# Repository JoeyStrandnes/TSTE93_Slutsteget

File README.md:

# TSTE93_Slutsteget
Projekt för kursen TSTE93

### Electronics

### Case

### Functional diagram

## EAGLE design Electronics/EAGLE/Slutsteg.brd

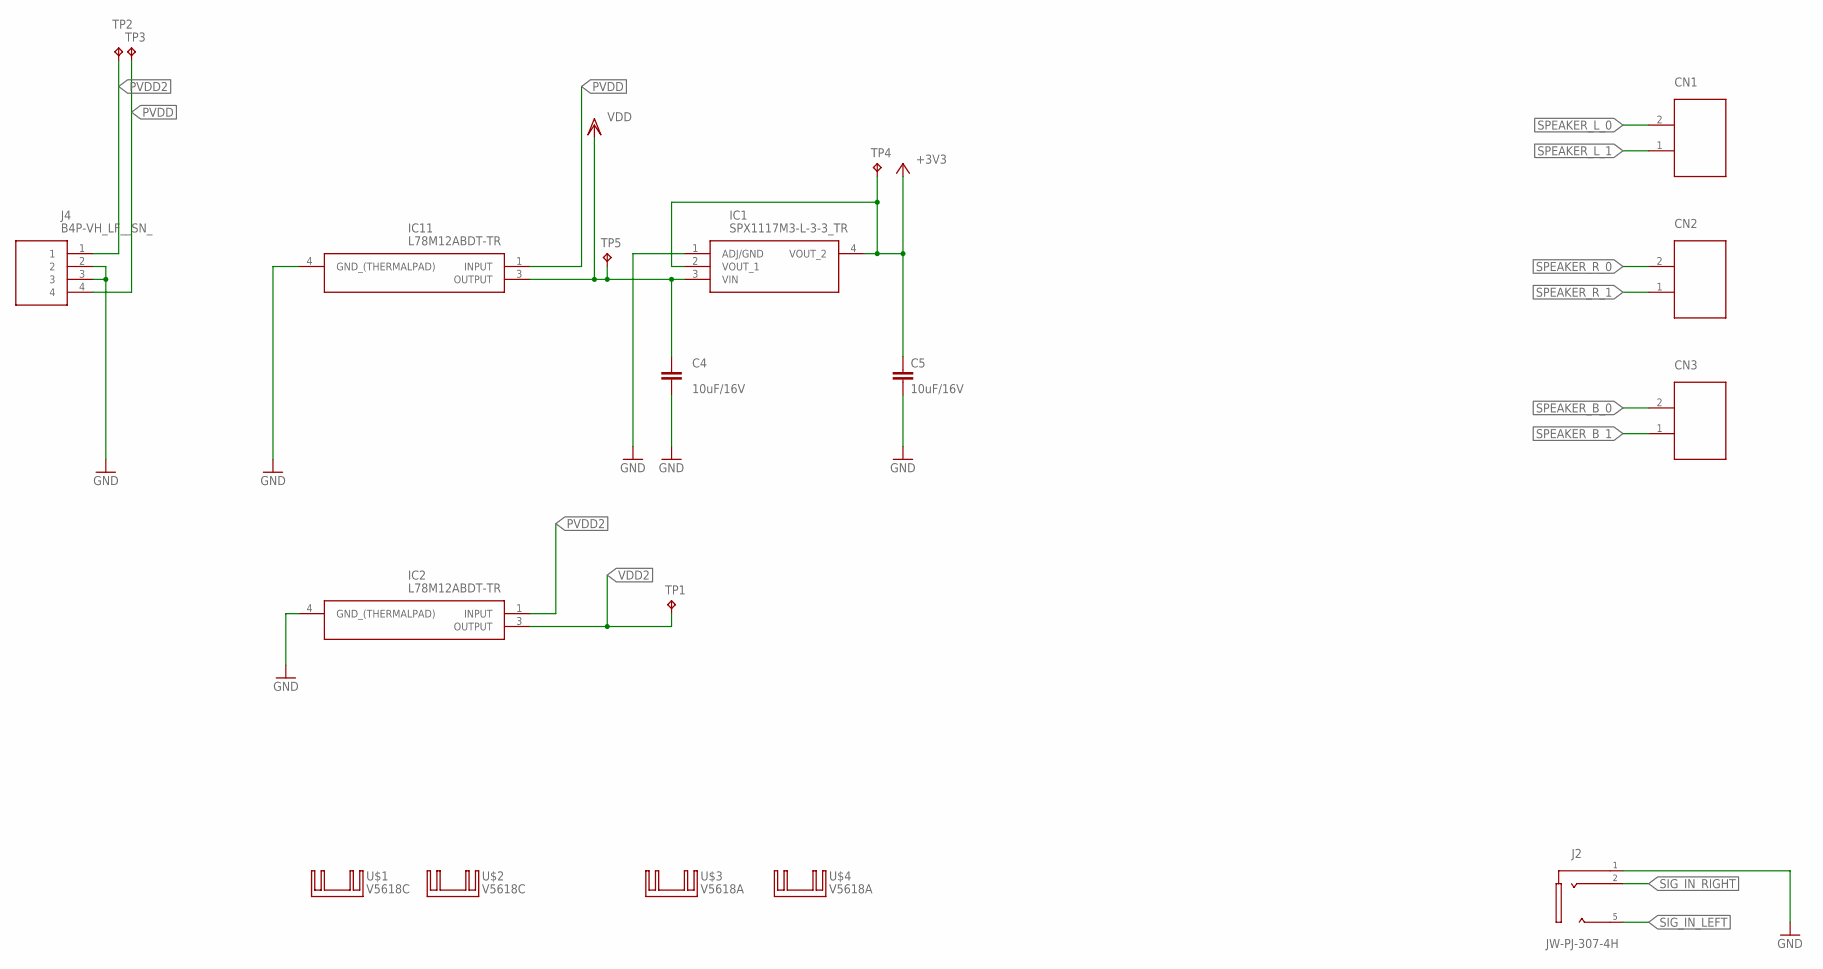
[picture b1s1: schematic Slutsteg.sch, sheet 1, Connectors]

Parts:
C4, C5: 10uF/16V; C0805
CN1, CN2, CN3: OSTYK33102030-2; OSTYK33108030-2
IC1: SPX1117M3-L-3-3_TR; SOT230P700X180-4N
IC2, IC11: L78M12ABDT-TR; TO228P972X240-3N
J2: JW-PJ-307-4H
J4: B4P-VH_LF__SN_; SHDR4W114P0X396_1X4_1578X850X9
TP1: TPB2,54; B2,54
TP2, TP3, TP4, TP5: TPB1,27; B1,27
U$1, U$2: V5618C
U$3, U$4: V5618A

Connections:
+3V3: C5.1, IC1.2 (VOUT_1), IC1.4 (VOUT_2), TP4.TP; also elsewhere on the board
GND: C4.2, C5.2, IC1.1 (ADJ/GND), IC2.4 (GND_(THERMALPAD)), IC11.4 (GND_(THERMALPAD)), J2.1, J4.2, J4.3; also elsewhere on the board
PVDD: IC11.1 (INPUT), J4.4, TP3.TP; also elsewhere on the board
PVDD2: IC2.1 (INPUT), J4.1, TP2.TP; also elsewhere on the board
SIG_IN_LEFT: J2.5; also elsewhere on the board
SIG_IN_RIGHT: J2.2; also elsewhere on the board
SPEAKER_B_0: CN3.2; also elsewhere on the board
SPEAKER_B_1: CN3.1; also elsewhere on the board
SPEAKER_L_0: CN1.2; also elsewhere on the board
SPEAKER_L_1: CN1.1; also elsewhere on the board
SPEAKER_R_0: CN2.2; also elsewhere on the board
SPEAKER_R_1: CN2.1; also elsewhere on the board
VDD: C4.1, IC1.3 (VIN), IC11.3 (OUTPUT), TP5.TP; also elsewhere on the board
VDD2: IC2.3 (OUTPUT), TP1.TP; also elsewhere on the board

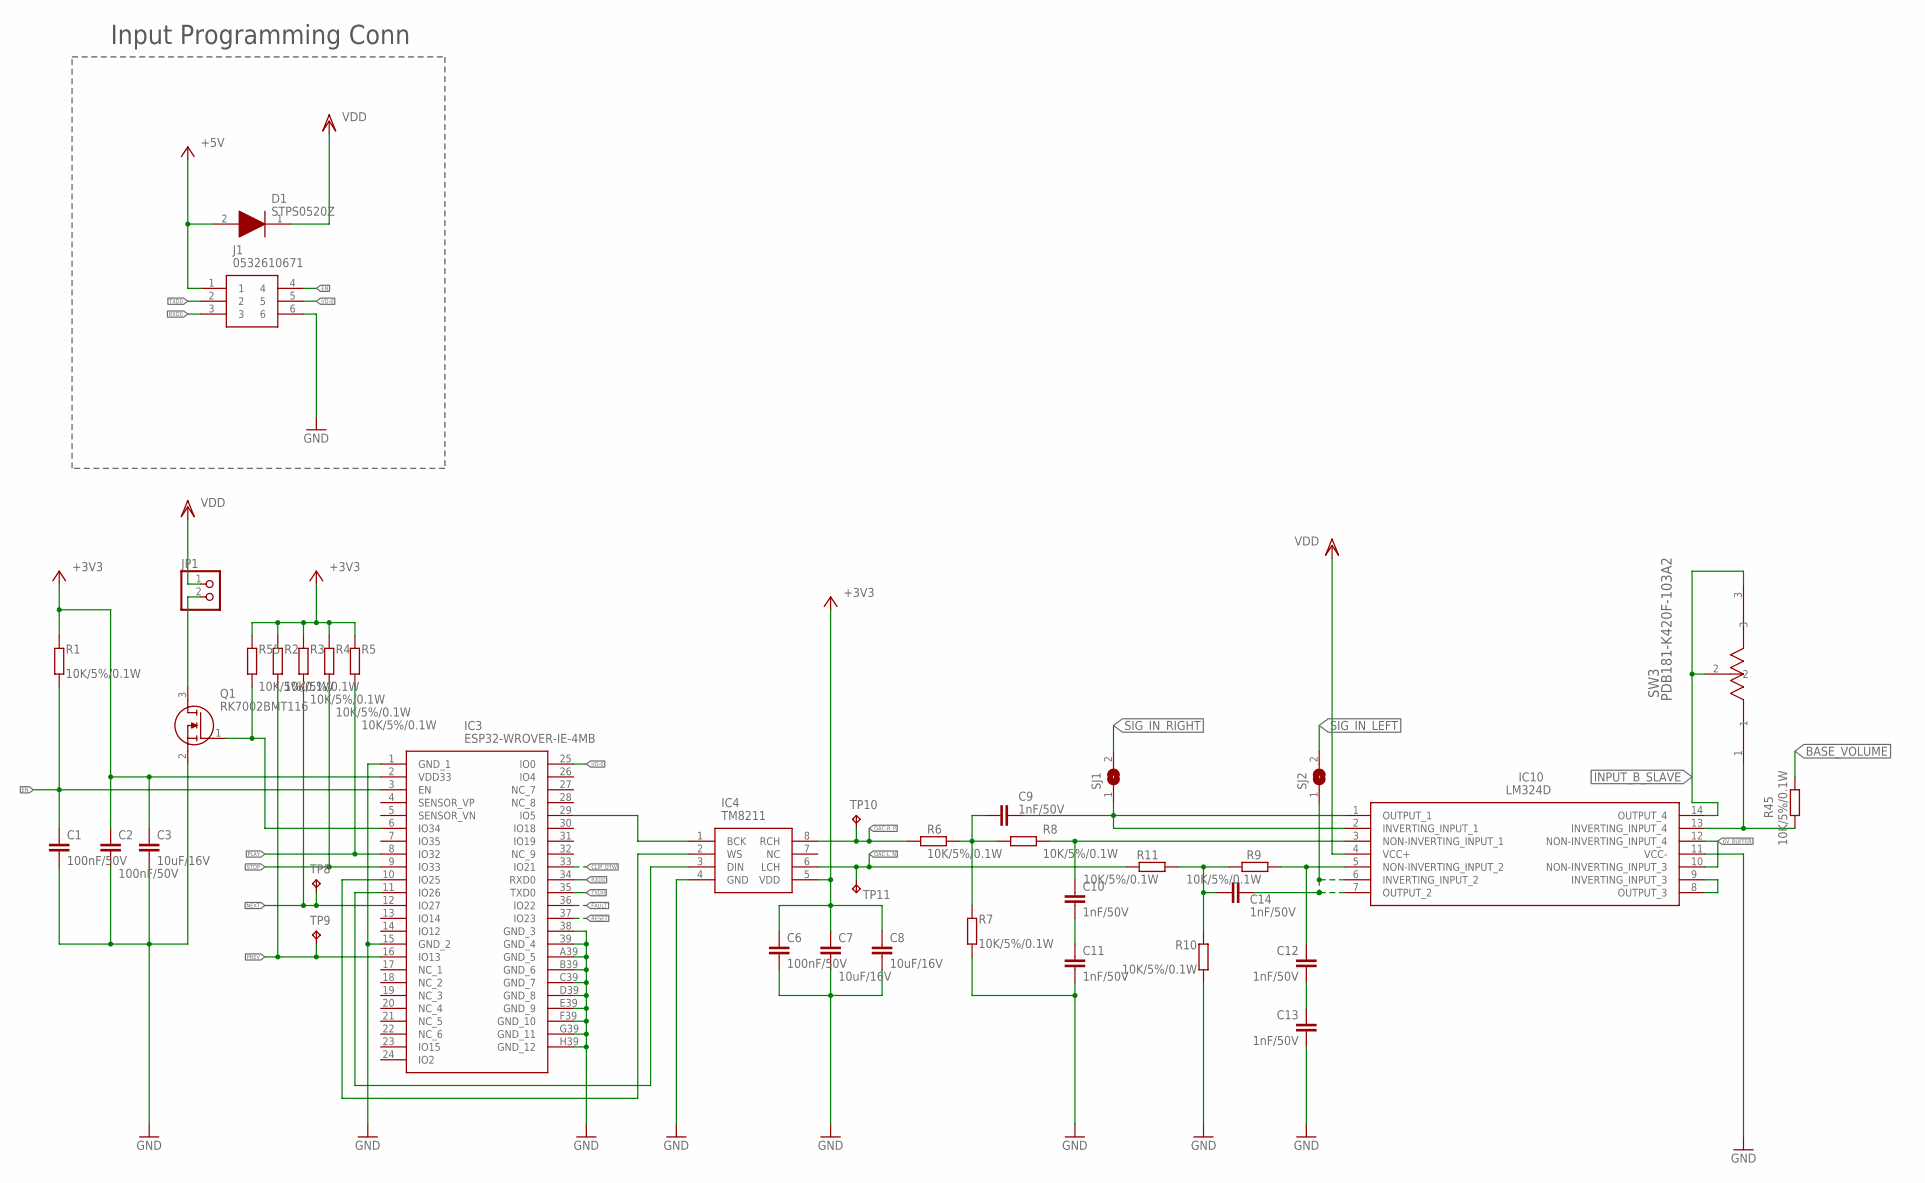
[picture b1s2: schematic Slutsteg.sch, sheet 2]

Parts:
C1, C2, C6: 100nF/50V; C0603
C3, C7, C8: 10uF/16V; C0805
C9, C10, C11, C12, C13, C14: 1nF/50V; C0603
D1: STPS0520Z; SOD3816X145N
IC3: ESP32-WROVER-IE-4MB; ESP32WROVERE8MB
IC4: TM8211; SOIC127P600X196-8N
IC10: LM324D; SOIC127P600X175-14N
J1: 0532610671
JP1: PINHD-1X2; 1X02
Q1: RK7002BMT116; BSS64AHZGT116
R1, R2, R3, R4, R5, R6, R7, R8, R9, R10, R11, R45, R55: 10K/5%/0.1W; R0603
SJ1, SJ2: SJ
SW3: PDB181-K420F-103A2; SW_420F-103A2_BRN
TP8, TP9, TP10, TP11: TPB1,27; B1,27

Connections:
6V_BUFFER: IC10.10 (NON-INVERTING_INPUT_3), IC10.12 (NON-INVERTING_INPUT_4); also elsewhere on the board
+3V3: C2.1, C3.1, C6.1, C7.1, C8.1, IC3.2 (VDD33), IC4.5 (VDD), R1.1, R2.1, R3.1, R4.1, R5.1, R55.1; also elsewhere on the board
+5V: D1.2 (A), J1.1
BASE_VOLUME: R45.1; also elsewhere on the board
CLIP_OTW: IC3.33 (IO21); also elsewhere on the board
DAC-L_N: IC4.6 (LCH), R11.1, TP11.TP
DAC-R_P: IC4.8 (RCH), R6.2, TP10.TP
EN: C1.1, IC3.3 (EN), J1.4, R1.2
FAULT: IC3.36 (IO22); also elsewhere on the board
GND: C1.2, C2.2, C3.2, C6.2, C7.2, C8.2, C11.2, C13.2, IC3.1 (GND_1), IC3.15 (GND_2), IC3.38 (GND_3), IC3.39 (GND_4), IC3.A39 (GND_5), IC3.B39 (GND_6), IC3.C39 (GND_7), IC3.D39 (GND_8), IC3.E39 (GND_9), IC3.F39 (GND_10), IC3.G39 (GND_11), IC3.H39 (GND_12), IC4.4 (GND), IC10.11 (VCC-), J1.6, Q1.2 (S), R7.2, R10.2; also elsewhere on the board
GSDJT: C9.1, IC10.1 (OUTPUT_1), IC10.2 (INVERTING_INPUT_1), SJ1.1
I/O-0: IC3.25 (IO0), J1.5
INPUT_B_SLAVE: IC10.14 (OUTPUT_4), SW3.2, SW3.3; also elsewhere on the board
unnamed: IC10.13 (INVERTING_INPUT_4), R45.2, SW3.1
unnamed: IC10.8 (OUTPUT_3), IC10.9 (INVERTING_INPUT_3)
unnamed: IC3.6 (IO34), Q1.1 (G), R55.2
unnamed: JP1.2, Q1.3 (D)
unnamed: IC3.11 (IO26), IC4.3 (DIN)
unnamed: IC3.29 (IO5), IC4.1 (BCK)
unnamed: IC3.10 (IO25), IC4.2 (WS)
unnamed: C10.1, IC10.3 (NON-INVERTING_INPUT_1), R8.1
unnamed: C10.2, C11.1
unnamed: C12.1, IC10.5 (NON-INVERTING_INPUT_2), R9.2
unnamed: C12.2, C13.1
unnamed: C14.2, R9.1, R10.1, R11.2
unnamed: C9.2, R6.1, R7.1, R8.2
NEXT: IC3.12 (IO27), R3.2, TP8.TP
PLAY: IC3.8 (IO32), R5.2
PREV: IC3.16 (IO13), R2.2, TP9.TP
RESET: IC3.37 (IO23); also elsewhere on the board
RXD0: IC3.34 (RXD0), J1.3
SIG_IN_LEFT: SJ2.2; also elsewhere on the board
SIG_IN_RIGHT: SJ1.2; also elsewhere on the board
STOP: IC3.9 (IO33), R4.2
TGHJESYRJK: C14.1, IC10.6 (INVERTING_INPUT_2), IC10.7 (OUTPUT_2), SJ2.1
TXD0: IC3.35 (TXD0), J1.2
VDD: D1.1 (K), IC10.4 (VCC+), JP1.1; also elsewhere on the board

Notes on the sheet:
Input Programming Conn

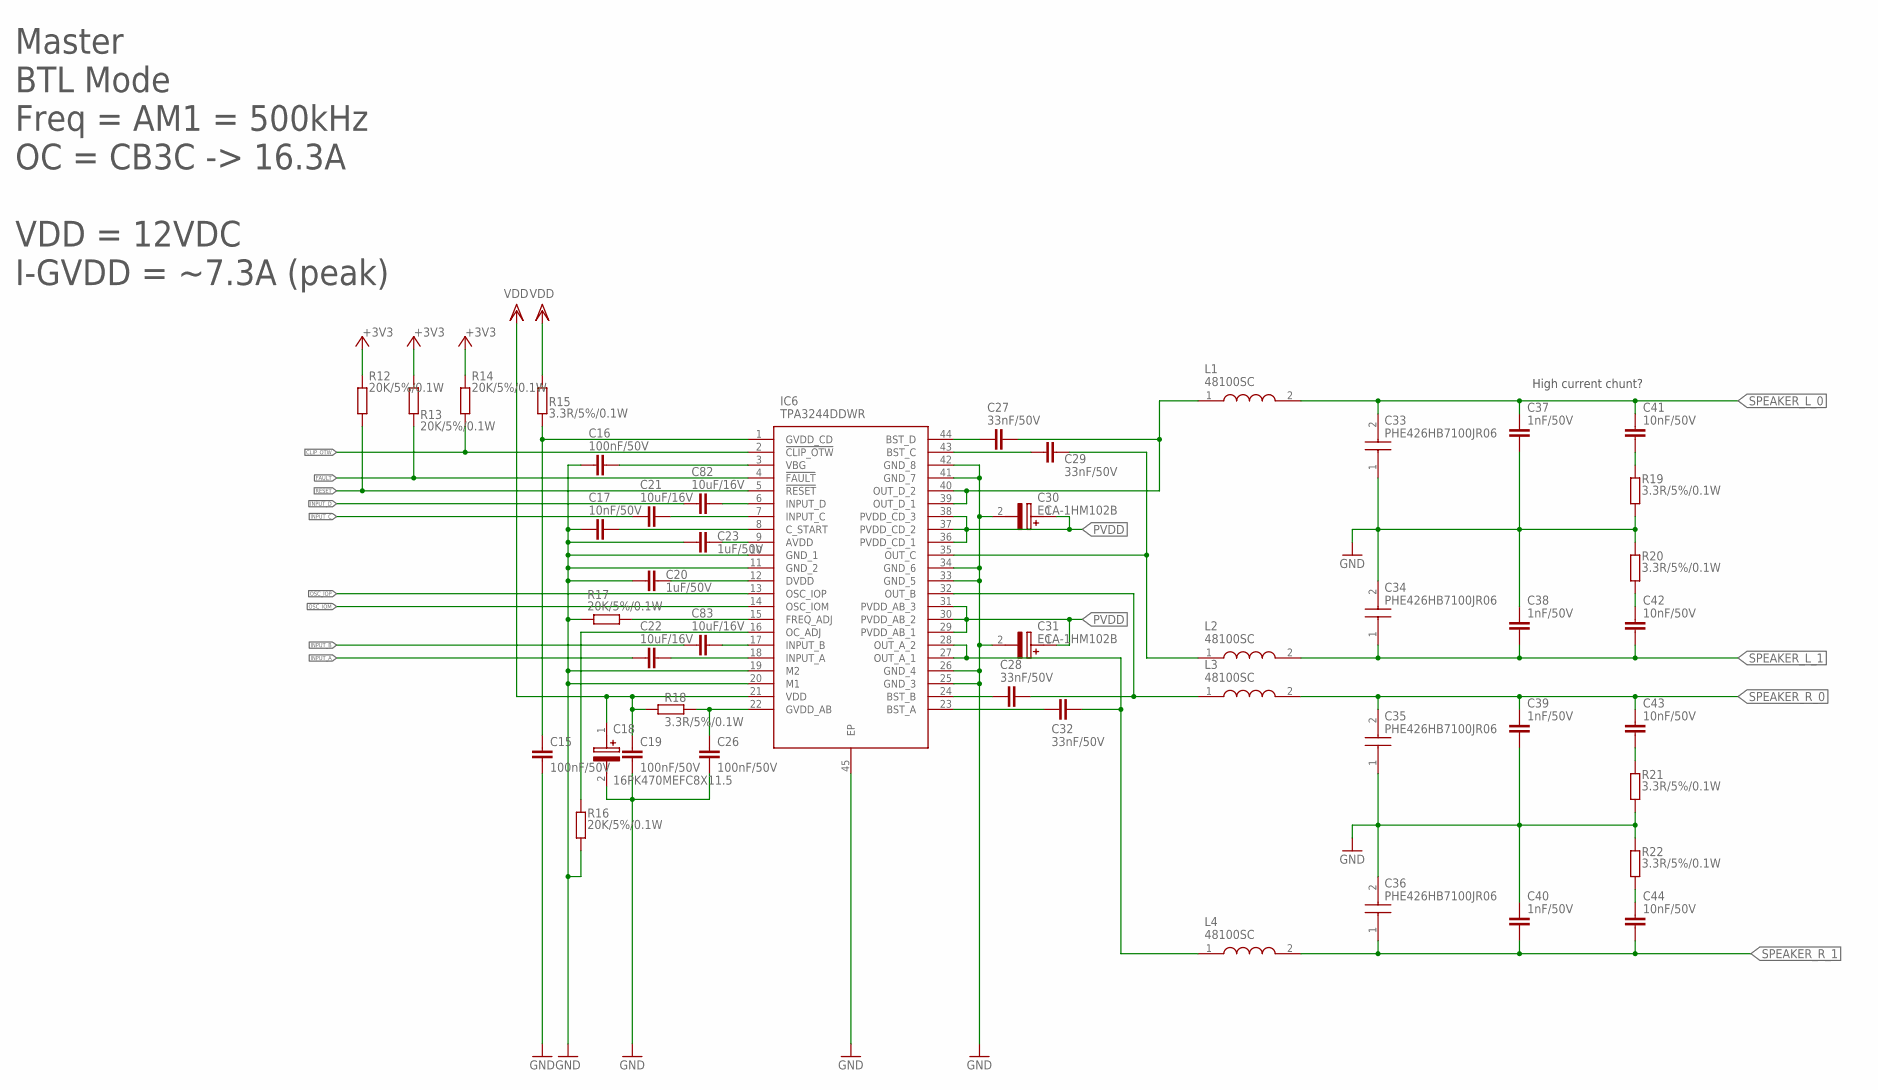
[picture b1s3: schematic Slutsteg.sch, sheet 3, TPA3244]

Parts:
C15, C16, C19, C26: 100nF/50V; C0603
C17, C41, C42, C43, C44: 10nF/50V; C0603
C18: 16PK470MEFC8X11.5; CAPPRD350W60D825H1300
C20, C23: 1uF/50V; C0805
C21, C22, C82, C83: 10uF/16V; C0805
C27, C28, C29, C32: 33nF/50V; C0603
C30, C31: ECA-1HM102B; CAPPRD500W60D1300H2650
C33, C34, C35, C36: PHE426HB7100JR06
C37, C38, C39, C40: 1nF/50V; C0603
IC6: TPA3244DDWR; SOP64P810X120-45N
L1, L2, L3, L4: 48100SC; INDPM122122X600N
R12, R13, R14, R16, R17: 20K/5%/0.1W; R0603
R15, R18, R19, R20, R21, R22: 3.3R/5%/0.1W; R0603

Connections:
+3V3: R12.2, R13.2, R14.2; also elsewhere on the board
CLIP_OTW: IC6.2 (!CLIP_OTW), R14.1; also elsewhere on the board
FAULT: IC6.4 (!FAULT), R13.1; also elsewhere on the board
GND: C15.2, C16.2, C17.2, C18.2 (-), C19.2, C20.1, C23.1, C26.2, C30.2 (-), C31.2 (-), C33.1, C34.2, C35.1, C36.2, C37.2, C38.1, C39.2, C40.1, IC6.10 (GND_1), IC6.11 (GND_2), IC6.19 (M2), IC6.20 (M1), IC6.25 (GND_3), IC6.26 (GND_4), IC6.33 (GND_5), IC6.34 (GND_6), IC6.41 (GND_7), IC6.42 (GND_8), IC6.45 (EP), R16.1, R17.1, R19.1, R20.2, R21.1, R22.2; also elsewhere on the board
INPUT_A: C22.1; also elsewhere on the board
INPUT_B: C83.1; also elsewhere on the board
INPUT_C: C21.1; also elsewhere on the board
INPUT_D: C82.1; also elsewhere on the board
unnamed: C20.2, IC6.12 (DVDD)
unnamed: C82.2, IC6.6 (INPUT_D)
unnamed: C83.2, IC6.17 (INPUT_B)
unnamed: C27.1, IC6.44 (BST_D)
unnamed: C29.1, IC6.43 (BST_C)
unnamed: C41.2, R19.2
unnamed: C42.1, R20.1
unnamed: C28.1, IC6.24 (BST_B)
unnamed: C32.1, IC6.23 (BST_A)
unnamed: C43.2, R21.2
unnamed: C44.1, R22.1
unnamed: IC6.15 (FREQ_ADJ), R17.2
unnamed: C16.1, IC6.3 (VBG)
unnamed: C17.1, IC6.8 (C_START)
unnamed: C23.2, IC6.9 (AVDD)
unnamed: C15.1, IC6.1 (GVDD_CD), R15.1
unnamed: C26.1, IC6.22 (GVDD_AB), R18.1
unnamed: C21.2, IC6.7 (INPUT_C)
unnamed: C22.2, IC6.18 (INPUT_A)
unnamed: IC6.16 (OC_ADJ), R16.2
OSC_IOM: IC6.14 (OSC_IOM); also elsewhere on the board
OSC_IOP: IC6.13 (OSC_IOP); also elsewhere on the board
OUT_A: C32.2, IC6.27 (OUT_A_1), IC6.28 (OUT_A_2), L4.1
OUT_B: C28.2, IC6.32 (OUT_B), L3.1
OUT_C: C29.2, IC6.35 (OUT_C), L2.1
OUT_D: C27.2, IC6.39 (OUT_D_1), IC6.40 (OUT_D_2), L1.1
PVDD: C30.1 (+), C31.1 (+), IC6.29 (PVDD_AB_1), IC6.30 (PVDD_AB_2), IC6.31 (PVDD_AB_3), IC6.36 (PVDD_CD_1), IC6.37 (PVDD_CD_2), IC6.38 (PVDD_CD_3); also elsewhere on the board
RESET: IC6.5 (!RESET), R12.1; also elsewhere on the board
SPEAKER_L_0: C33.2, C37.1, C41.1, L1.2; also elsewhere on the board
SPEAKER_L_1: C34.1, C38.2, C42.2, L2.2; also elsewhere on the board
SPEAKER_R_0: C35.2, C39.1, C43.1, L3.2; also elsewhere on the board
SPEAKER_R_1: C36.1, C40.2, C44.2, L4.2; also elsewhere on the board
VDD: C18.1 (+), C19.1, IC6.21 (VDD), R15.2, R18.2; also elsewhere on the board

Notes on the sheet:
High current chunt?
Master BTL Mode Freq = AM1 = 500kHz OC = CB3C -> 16.3A VDD = 12VDC I-GVDD = ~7.3A (peak)

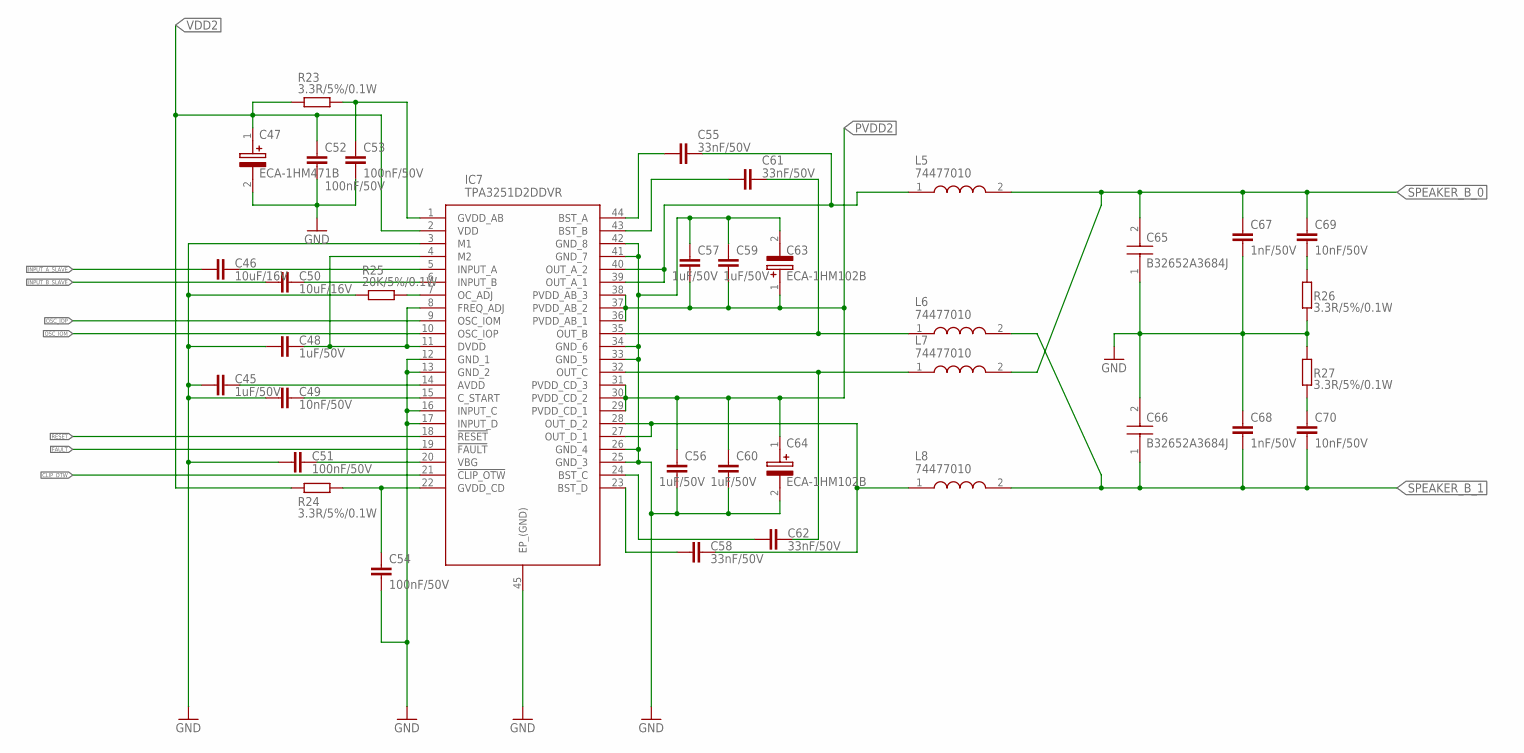
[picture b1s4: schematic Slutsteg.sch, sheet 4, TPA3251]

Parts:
C45, C48, C56, C57, C59, C60: 1uF/50V; C0805
C46, C50: 10uF/16V; C0805
C47: ECA-1HM471B; CAPPRD350W60D825H1300
C49, C69, C70: 10nF/50V; C0603
C51, C52, C53, C54: 100nF/50V; C0603
C55, C58, C61, C62: 33nF/50V; C0603
C63, C64: ECA-1HM102B; CAPPRD500W60D1300H2650
C65, C66: B32652A3684J
C67, C68: 1nF/50V; C0603
IC7: TPA3251D2DDVR; SOP64P810X120-45N@1
L5, L6, L7, L8: 74477010; WE-PD_1260/1245/1280/121054
R23, R24, R26, R27: 3.3R/5%/0.1W; R0603
R25: 20K/5%/0.1W; R0603

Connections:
CLIP_OTW: IC7.21 (!CLIP_OTW); also elsewhere on the board
FAULT: IC7.19 (!FAULT); also elsewhere on the board
GND: C45.1, C47.2 (-), C48.1, C49.1, C51.1, C52.2, C53.2, C54.2, C56.2, C57.1, C59.1, C60.2, C63.2 (-), C64.2 (-), C65.1, C66.2, C67.2, C68.1, IC7.3 (M1), IC7.12 (GND_1), IC7.13 (GND_2), IC7.16 (INPUT_C), IC7.17 (INPUT_D), IC7.25 (GND_3), IC7.26 (GND_4), IC7.33 (GND_5), IC7.34 (GND_6), IC7.41 (GND_7), IC7.42 (GND_8), IC7.45 (EP_(GND)), R25.1, R26.1, R27.2; also elsewhere on the board
INPUT_A_SLAVE: C46.2; also elsewhere on the board
INPUT_B_SLAVE: C50.2; also elsewhere on the board
unnamed: C70.1, R27.1
unnamed: C55.1, IC7.44 (BST_A)
unnamed: C55.2, IC7.39 (OUT_A_1), IC7.40 (OUT_A_2), L5.1
unnamed: C61.2, IC7.35 (OUT_B), L6.1
unnamed: C58.1, IC7.23 (BST_D)
unnamed: C62.1, IC7.24 (BST_C)
unnamed: C62.2, IC7.32 (OUT_C), L7.1
unnamed: C46.1, IC7.5 (INPUT_A)
unnamed: C50.1, IC7.6 (INPUT_B)
unnamed: C53.1, IC7.1 (GVDD_AB), R23.2
unnamed: C51.2, IC7.20 (VBG)
unnamed: C49.2, IC7.15 (C_START)
unnamed: C45.2, IC7.14 (AVDD)
unnamed: C48.2, IC7.4 (M2), IC7.8 (FREQ_ADJ), IC7.11 (DVDD)
unnamed: IC7.7 (OC_ADJ), R25.2
unnamed: C61.1, IC7.43 (BST_B)
unnamed: C58.2, IC7.27 (OUT_D_1), IC7.28 (OUT_D_2), L8.1
unnamed: C54.1, IC7.22 (GVDD_CD), R24.2
unnamed: C69.2, R26.2
OSC_IOM: IC7.10 (OSC_IOP); also elsewhere on the board
OSC_IOP: IC7.9 (OSC_IOM); also elsewhere on the board
PVDD2: C56.1, C57.2, C59.2, C60.1, C63.1 (+), C64.1 (+), IC7.29 (PVDD_CD_1), IC7.30 (PVDD_CD_2), IC7.31 (PVDD_CD_3), IC7.36 (PVDD_AB_1), IC7.37 (PVDD_AB_2), IC7.38 (PVDD_AB_3); also elsewhere on the board
RESET: IC7.18 (!RESET); also elsewhere on the board
SPEAKER_B_0: C65.2, C67.1, C69.1, L5.2, L7.2; also elsewhere on the board
SPEAKER_B_1: C66.1, C68.2, C70.2, L6.2, L8.2; also elsewhere on the board
VDD2: C47.1 (+), C52.1, IC7.2 (VDD), R23.1, R24.1; also elsewhere on the board

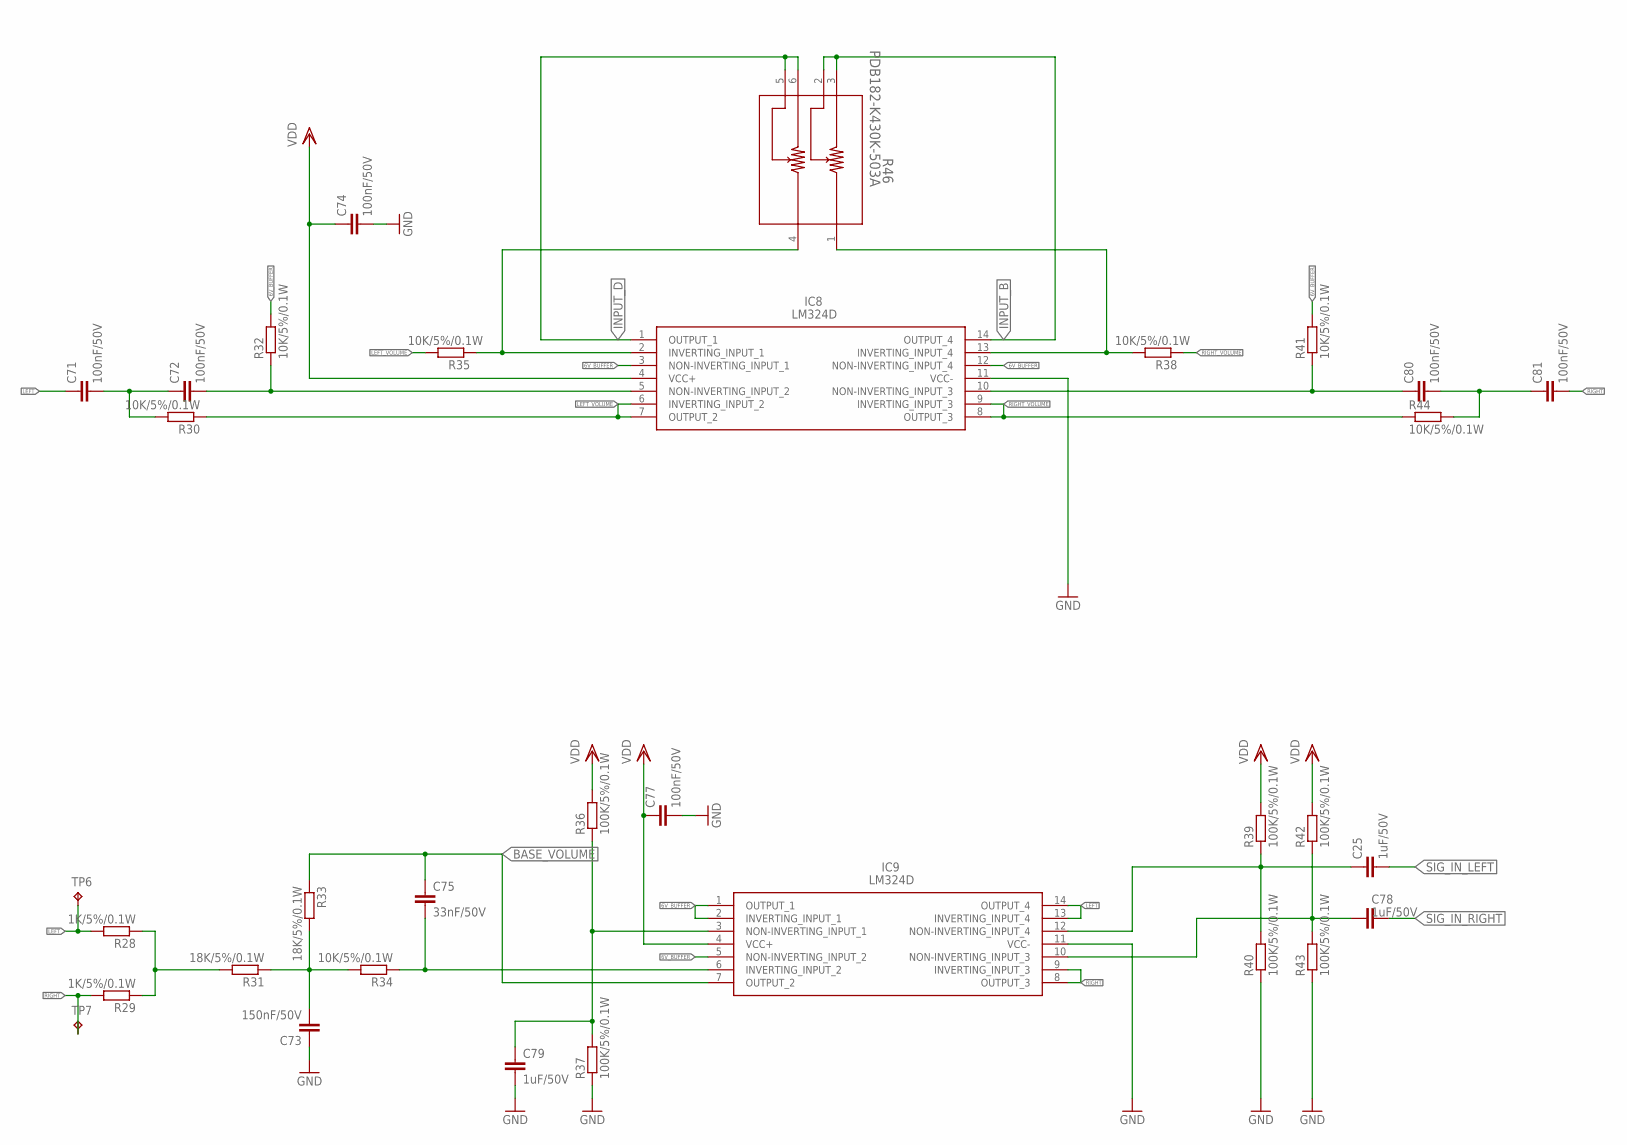
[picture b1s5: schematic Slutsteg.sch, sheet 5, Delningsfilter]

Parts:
C25, C78, C79: 1uF/50V; C0805
C71, C72, C74, C77, C80, C81: 100nF/50V; C0603
C73: 150nF/50V; C0603
C75: 33nF/50V; C0603
IC8, IC9: LM324D; SOIC127P600X175-14N
R28, R29: 1K/5%/0.1W; R0603
R30, R32, R34, R35, R38, R41, R44: 10K/5%/0.1W; R0603
R31, R33: 18K/5%/0.1W; R0603
R36, R37, R39, R40, R42, R43: 100K/5%/0.1W; R0603
R46: PDB182-K430K-503A; PDB18-2
TP6, TP7: TPB1,27; B1,27

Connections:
6V_BUFFER: IC8.3 (NON-INVERTING_INPUT_1), IC8.12 (NON-INVERTING_INPUT_4), IC9.1 (OUTPUT_1), IC9.2 (INVERTING_INPUT_1), IC9.5 (NON-INVERTING_INPUT_2), R32.2, R41.2; also elsewhere on the board
BASE_VOLUME: C75.1, IC9.7 (OUTPUT_2), R33.1; also elsewhere on the board
GND: C73.1, C74.2, C77.2, C79.2, IC8.11 (VCC-), IC9.11 (VCC-), R37.1, R40.1, R43.1; also elsewhere on the board
INPUT_B: IC8.14 (OUTPUT_4), R46.2, R46.3; also elsewhere on the board
INPUT_D: IC8.1 (OUTPUT_1), R46.5, R46.6; also elsewhere on the board
LEFT: C71.1, IC9.13 (INVERTING_INPUT_4), IC9.14 (OUTPUT_4), R28.2, TP6.TP
LEFT_VOLUME: IC8.6 (INVERTING_INPUT_2), IC8.7 (OUTPUT_2), R30.1, R35.2
unnamed: C25.1, IC9.12 (NON-INVERTING_INPUT_4), R39.1, R40.2
unnamed: C78.1, IC9.10 (NON-INVERTING_INPUT_3), R42.1, R43.2
unnamed: C79.1, IC9.3 (NON-INVERTING_INPUT_1), R36.1, R37.2
unnamed: R28.1, R29.1, R31.2
unnamed: C73.2, R31.1, R33.2, R34.2
unnamed: C75.2, IC9.6 (INVERTING_INPUT_2), R34.1
unnamed: C71.2, C72.1, R30.2
unnamed: C72.2, IC8.5 (NON-INVERTING_INPUT_2), R32.1
unnamed: IC8.2 (INVERTING_INPUT_1), R35.1, R46.4
unnamed: C80.1, IC8.10 (NON-INVERTING_INPUT_3), R41.1
unnamed: C80.2, C81.1, R44.2
unnamed: IC8.13 (INVERTING_INPUT_4), R38.2, R46.1
RIGHT: C81.2, IC9.8 (OUTPUT_3), IC9.9 (INVERTING_INPUT_3), R29.2, TP7.TP
RIGHT_VOLUME: IC8.8 (OUTPUT_3), IC8.9 (INVERTING_INPUT_3), R38.1, R44.1
SIG_IN_LEFT: C25.2; also elsewhere on the board
SIG_IN_RIGHT: C78.2; also elsewhere on the board
VDD: C74.1, C77.1, IC8.4 (VCC+), IC9.4 (VCC+), R36.2, R39.2, R42.2; also elsewhere on the board

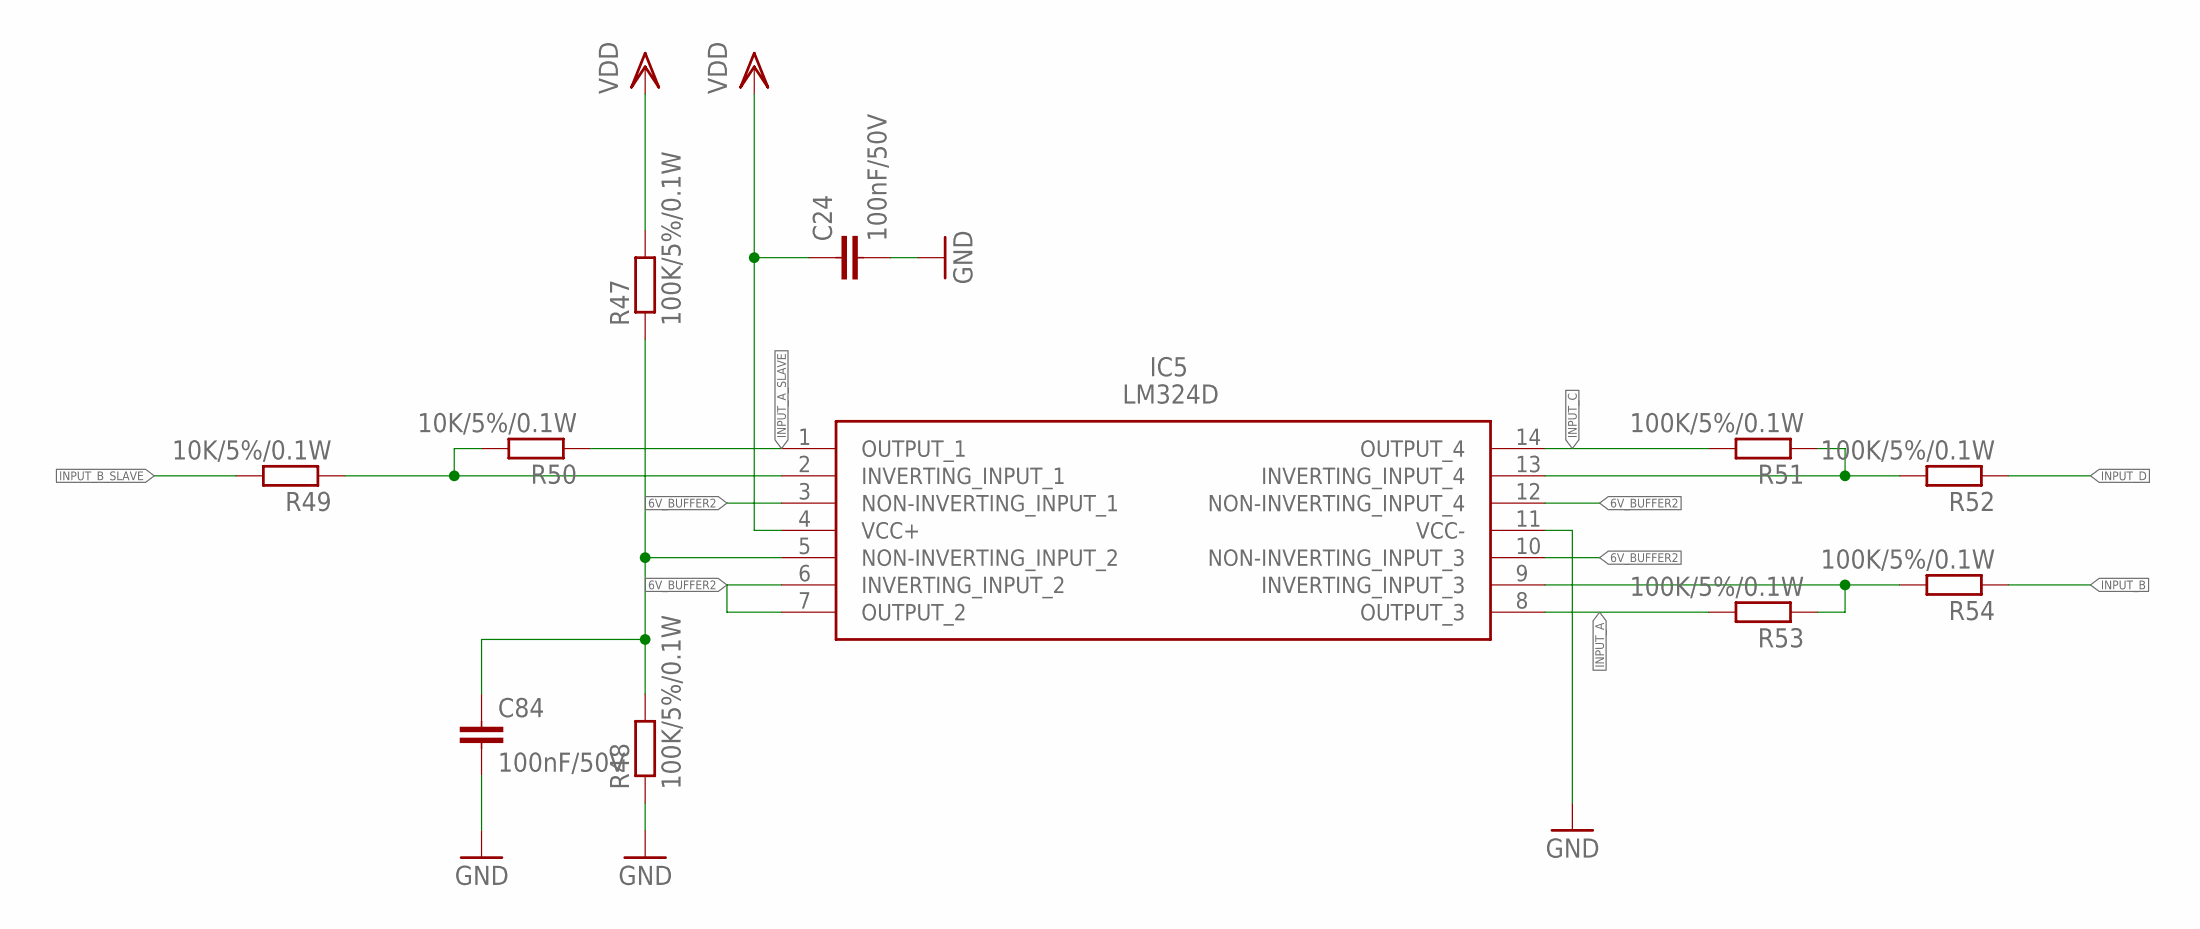
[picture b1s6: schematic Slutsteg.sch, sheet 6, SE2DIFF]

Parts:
C24, C84: 100nF/50V; C0603
IC5: LM324D; SOIC127P600X175-14N
R47, R48, R51, R52, R53, R54: 100K/5%/0.1W; R0603
R49, R50: 10K/5%/0.1W; R0603

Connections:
6V_BUFFER2: IC5.3 (NON-INVERTING_INPUT_1), IC5.6 (INVERTING_INPUT_2), IC5.7 (OUTPUT_2), IC5.10 (NON-INVERTING_INPUT_3), IC5.12 (NON-INVERTING_INPUT_4)
GND: C24.2, C84.2, IC5.11 (VCC-), R48.1; also elsewhere on the board
INPUT_A: IC5.8 (OUTPUT_3), R53.2; also elsewhere on the board
INPUT_A_SLAVE: IC5.1 (OUTPUT_1), R50.1; also elsewhere on the board
INPUT_B: R54.1; also elsewhere on the board
INPUT_B_SLAVE: R49.2; also elsewhere on the board
INPUT_C: IC5.14 (OUTPUT_4), R51.2; also elsewhere on the board
INPUT_D: R52.1; also elsewhere on the board
unnamed: C84.1, IC5.5 (NON-INVERTING_INPUT_2), R47.1, R48.2
unnamed: IC5.13 (INVERTING_INPUT_4), R51.1, R52.2
unnamed: IC5.2 (INVERTING_INPUT_1), R49.1, R50.2
unnamed: IC5.9 (INVERTING_INPUT_3), R53.1, R54.2
VDD: C24.1, IC5.4 (VCC+), R47.2; also elsewhere on the board

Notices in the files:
parts and their libraries:
COPYRIGHT: Copyright (C) 2018 Accelerated Designs. All rights reserved
